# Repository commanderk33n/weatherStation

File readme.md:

# Weather Station NodeMCU

#### Usage:

after checkout:

- Download Arduino IDE
- Download ESP8266 Development Board and Driver File:
    - File->Preferences 'Additional Boards Manager URLs:
      - http://arduino.esp8266.com/stable/package_esp8266com_index.json
    - Download esp8266 with Boards Manager
- Install Libaries:
    - esp8266 weather
    - JSON Streaming
    - adafruit bme280
    - adafruit Unified sensor
    - oled lib from NodeMCU/lib
- Add your WIFI, Webserver and Database-Server info into weatherSationKeen.ino, esp-chart.php and post-data.php

#### Hardware used:
- NodeMCU ESP8266 (CP2102)
- GY-BME280 Sensormodul
- OLED-Display (SSH1106)
- RaspberryPi for Webserver (Nginx, MariaDB, PHP)

#### Pin Connection:
- NodeMCU ESP8266 <-----> OLED
    - 3.3V---VCC
    - GND---GND
    - D1---SCL
    - D2---SDA
- NodeMCU ESP8266<-----> BME280
    - 3.3V---VCC
    - GND---GND
    - D1---SCL
    - D2---SDA

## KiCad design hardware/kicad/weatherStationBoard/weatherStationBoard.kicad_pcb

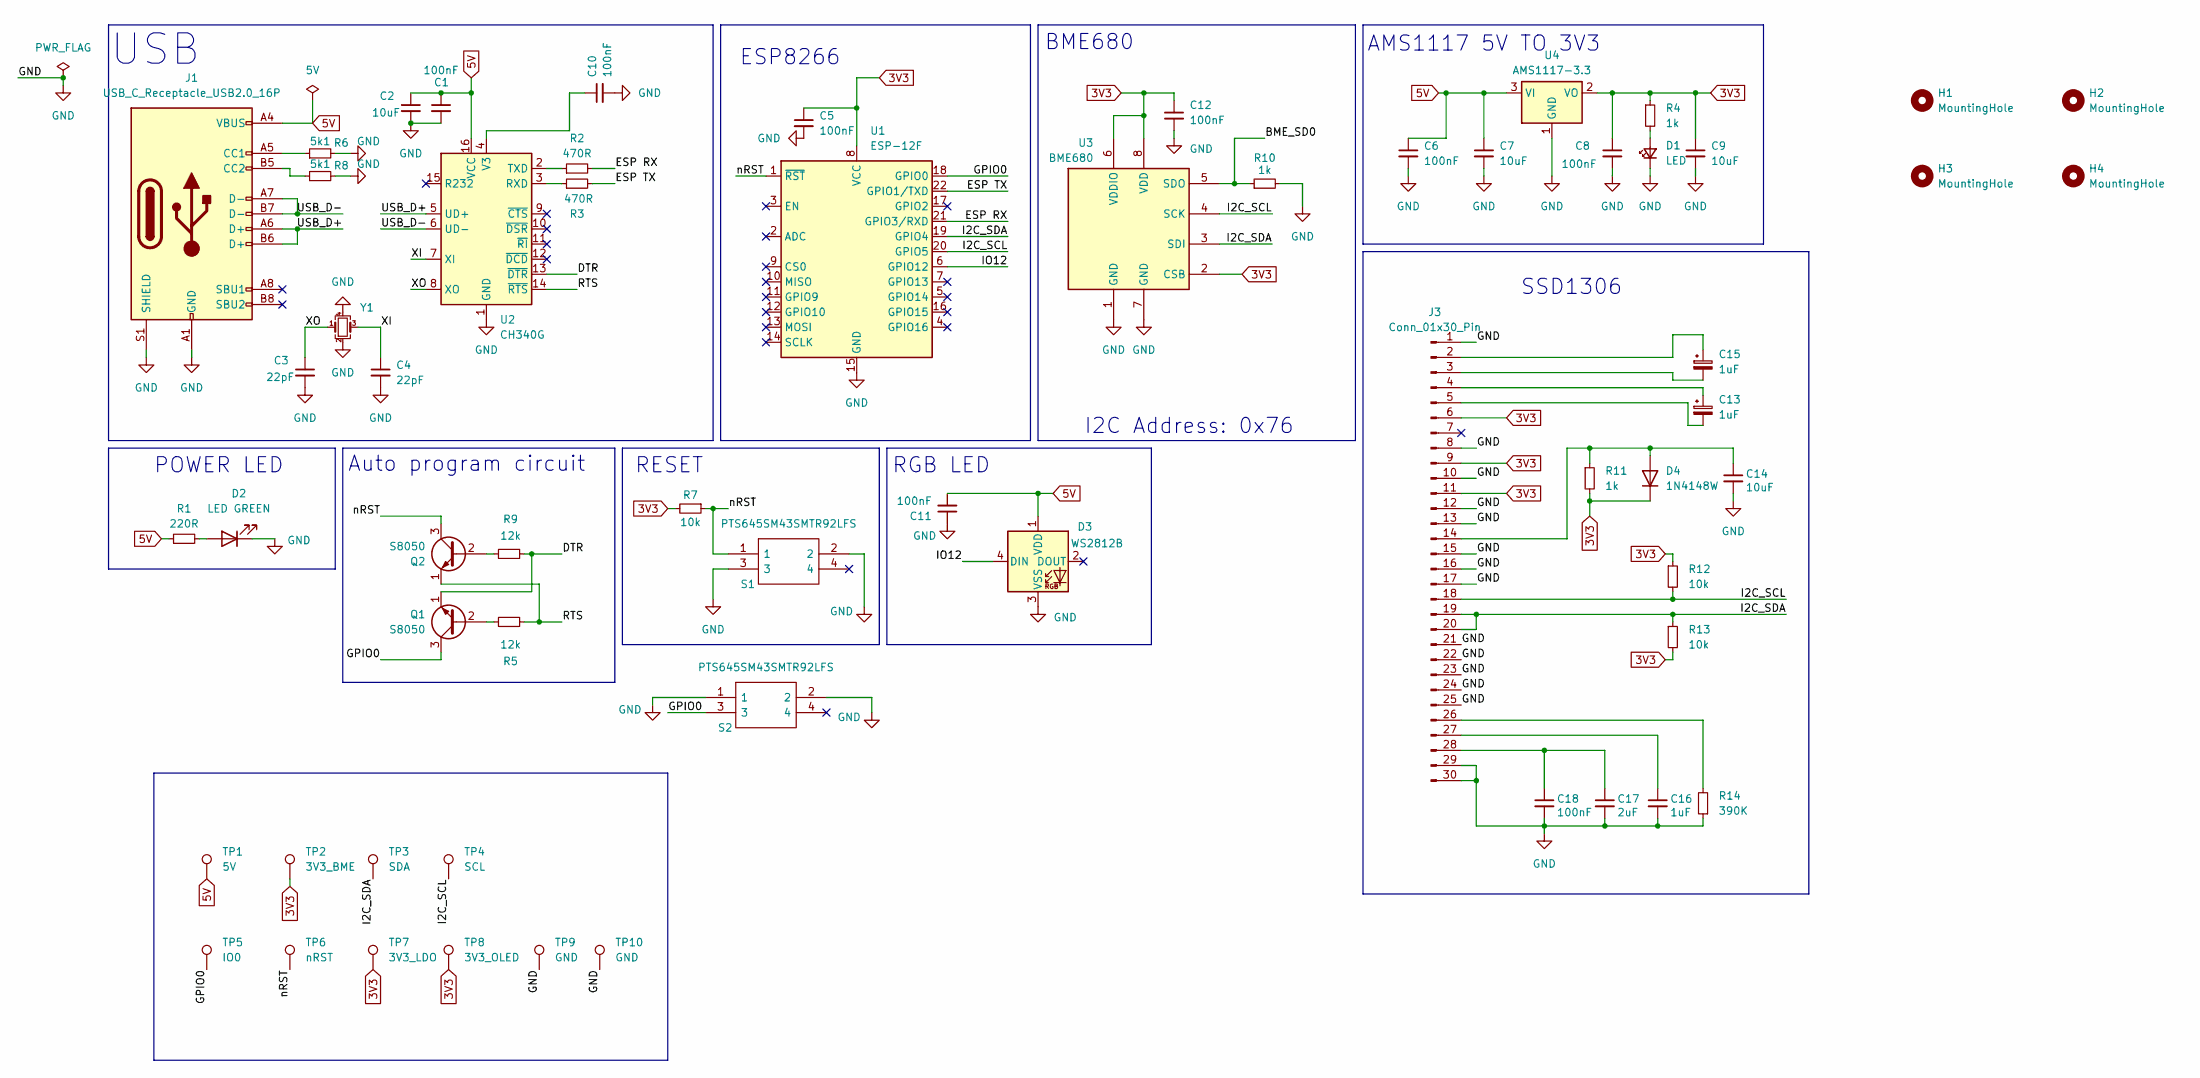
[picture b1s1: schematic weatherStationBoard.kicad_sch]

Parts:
C1, C5, C6, C8, C10, C11, C12, C18: 100nF; C_0805_2012Metric
C2, C7, C9, C14: 10uF; C_0805_2012Metric
C3, C4: 22pF; C_0805_2012Metric
C13, C15, C16: 1uF; C_0805_2012Metric
C17: 2uF; C_0805_2012Metric
D1: LED; LED_0805_2012Metric
D2: LED GREEN; LED_0805_2012Metric
D3: WS2812B; LED_WS2812B_PLCC4_5.0x5.0mm_P3.2mm
D4: 1N4148W; D_SOD-123
H1, H2, H3, H4: MountingHole; MountingHole_2.2mm_M2
J1: USB_C_Receptacle_USB2.0_16P; USB_C_Receptacle_HRO_TYPE-C-31-M-12
J3: Conn_01x30_Pin; SSD1306_ribbon
Q1, Q2: S8050; SOT-23-3
R1: 220R; R_0805_2012Metric
R2, R3: 470R; R_0805_2012Metric
R4, R10, R11: 1k; R_0805_2012Metric
R5, R9: 12k; R_0805_2012Metric
R6, R8: 5k1; R_0805_2012Metric
R7, R12, R13: 10k; R_0805_2012Metric
R14: 390K; R_0805_2012Metric
S1, S2: PTS645SM43SMTR92LFS; PTS645_SMT_; Manufacturer_Part_Number PTS645SM43SMTR92LFS; Mouser Part Number 611-PTS645SM43SMTR92
TP1: 5V; TestPoint_Pad_D1.0mm
TP2: 3V3_BME; TestPoint_Pad_D1.0mm
TP3: SDA; TestPoint_Pad_D1.0mm
TP4: SCL; TestPoint_Pad_D1.0mm
TP5: IO0; TestPoint_Pad_D1.0mm
TP6: nRST; TestPoint_Pad_D1.0mm
TP7: 3V3_LDO; TestPoint_Pad_D1.0mm
TP8: 3V3_OLED; TestPoint_Pad_D1.0mm
TP9, TP10: GND; TestPoint_Pad_D1.0mm
U1: ESP-12F; ESP-12E
U2: CH340G; SOIC-16_3.9x9.9mm_P1.27mm
U3: BME680; Bosch_LGA-8_3x3mm_P0.8mm_ClockwisePinNumbering
U4: AMS1117-3.3; SOT-223-3_TabPin2
Y1: Crystal_GND24_Small; Crystal_SMD_3225-4Pin_3.2x2.5mm

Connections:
3V3: C5.1, C8.1, C9.1, C12.1, D4.1 (K), J3.6, J3.9, J3.11, R4.1, R7.2, R11.2, R12.1, R13.2, TP2.1, TP7.1, TP8.1, U1.8 (VCC), U3.2 (CSB), U3.6 (VDDIO), U3.8 (VDD), U4.2 (VO)
5V: C1.1, C2.1, C6.1, C7.1, C11.2, D3.1 (VDD), J1.A4 (VBUS), J1.A9 (VBUS), J1.B4 (VBUS), J1.B9 (VBUS), R1.1, TP1.1, U2.16 (VCC), U4.3 (VI)
/BME_SD0: R10.1, U3.5 (SDO)
/DTR: Q1.1 (E), R9.2, U2.13 (~DTR)
/ESP RX: R2.2, U1.21 (GPIO3/RXD)
/ESP TX: R3.2, U1.22 (GPIO1/TXD)
/GPIO0: Q1.3 (C), S2.3, TP5.1, U1.18 (GPIO0)
/I2C_SCL: J3.18, R12.2, TP4.1, U1.20 (GPIO5), U3.4 (SCK)
/I2C_SDA: J3.19, J3.20, R13.1, TP3.1, U1.19 (GPIO4), U3.3 (SDI)
/IO12: D3.4 (DIN), U1.6 (GPIO12)
/RTS: Q2.1 (E), R5.2, U2.14 (~RTS)
/USB_D+: J1.A6 (D+), J1.B6 (D+), U2.5 (UD+)
/USB_D-: J1.A7 (D-), J1.B7 (D-), U2.6 (UD-)
/XI: C4.1, U2.7 (XI), Y1.3
/XO: C3.1, U2.8 (XO), Y1.1
/nRST: Q2.3 (C), R7.1, S1.1, TP6.1, U1.1 (~RST)
GND: C1.2, C2.2, C3.2, C4.2, C5.2, C6.2, C7.2, C8.2, C9.2, C10.2, C11.1, C12.2, C14.2, C16.2, C17.2, C18.2, D1.1 (K), D2.1 (K), D3.3 (VSS), J1.A1 (GND), J1.A12 (GND), J1.B1 (GND), J1.B12 (GND), J1.S1 (SHIELD), J3.1, J3.8, J3.10, J3.12, J3.13, J3.15, J3.16, J3.17, J3.21, J3.22, J3.23, J3.24, J3.25, J3.29, J3.30, R6.2, R8.2, R10.2, R14.1, S1.2, S1.3, S2.1, S2.2, TP9.1, TP10.1, U1.15 (GND), U2.1 (GND), U3.1 (GND), U3.7 (GND), U4.1 (GND), Y1.2, Y1.4
unnamed: D1.2 (A), R4.2
unnamed: D2.2 (A), R1.2
unnamed: C14.1, D4.2 (A), J3.14, R11.1
unnamed: J1.A5 (CC1), R6.1
unnamed: J1.B5 (CC2), R8.1
unnamed: C15.1, J3.2
unnamed: C15.2, J3.3
unnamed: C13.1, J3.4
unnamed: C13.2, J3.5
unnamed: J3.26, R14.2
unnamed: C16.1, J3.27
unnamed: C17.1, C18.1, J3.28
unnamed: Q1.2 (B), R5.1
unnamed: Q2.2 (B), R9.1
unnamed: R3.1, U2.3 (RXD)
unnamed: R2.1, U2.2 (TXD)
unnamed: C10.1, U2.4 (V3)

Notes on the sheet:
I2C Address: 0x76
SSD1306
BME680
RGB LED
RESET
ESP8266
Auto program circuit
USB
AMS1117 5V TO 3V3
POWER LED

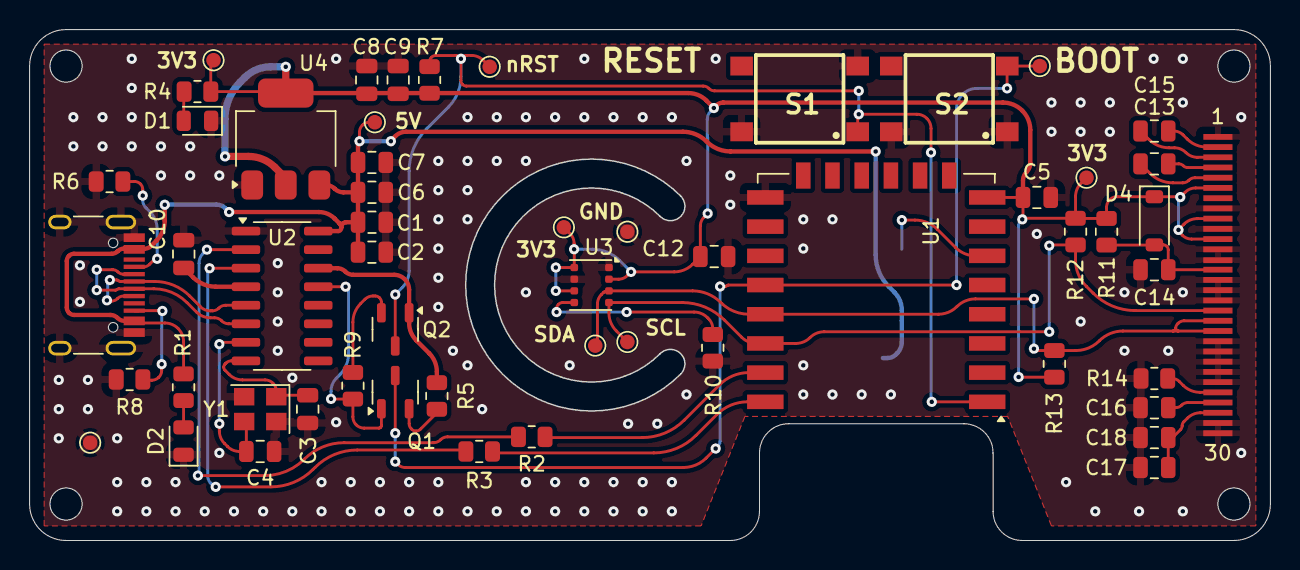
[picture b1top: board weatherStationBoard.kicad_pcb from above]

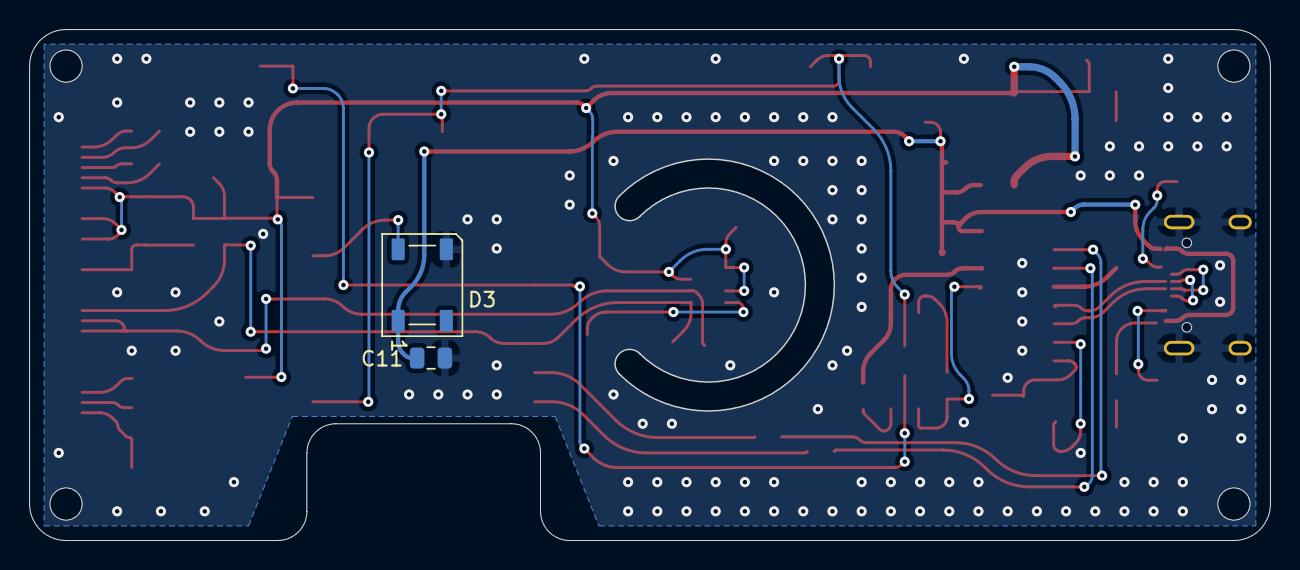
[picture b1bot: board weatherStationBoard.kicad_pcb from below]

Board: 4 copper layers, 85.0 x 35.0 mm, 61 parts (2 on the bottom side), 34 nets.

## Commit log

2020-10-29 makePOST() method
2024-10-15 Hardware files
2024-10-15 Display datasheet
2024-10-15 added gitignore
2024-10-15 Node mcu schematic
2024-10-15 Serial CH340 datasheet
2024-10-15 ignore local backups of kicad
2024-10-15 PCB Simple LED Circuit With Usb-C
2024-10-15 power, 5vto3v, usb to serial
2024-10-15 PCB updated
2024-10-16 Pushbutton files
2024-10-16 3D Model of Pushbutton
2024-10-16 Updated usb connector
2024-10-16 board design prototype no periphery
2024-10-17 Added BME680 Display-Connector and Mounting holes - 3D model of USB connector and Readme assets
2024-10-17 Added Readme
2024-10-17 Board&Case
2024-10-17 Testpoints added
2024-10-17 REV1 WeatherStationBoard
2024-10-18 Gerberfiles and final Case model
2024-10-18 improved step model and silkscreen export
